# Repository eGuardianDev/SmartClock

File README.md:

# SmartClock
A small "smart" alarm clock for IoT course.

### Idea
A small clock with alarm and basic functions. Integrationg with WiFi via ESP32 for data sharing, maybe smart home automation. Different sensors for tracking enviroment data and sleep patterns.

### Restart of project
 - [ ] Change from arduino ide to platformio
 - [ ] Refactor RTC functions
 - [ ] Refactor display functions
 - [ ] Refactor pages system
 - [ ] Refactor bme280 sensors
 - [ ] Add sleep mode
 - [ ] Fix button design
 - [ ] Add lights for the display

## Documentation

### Tools
 - [Bit map to code](https://www.teachmemicro.com/lcd-bitmap-converter-online/)

### Parts
- Display: probably E-Ink or 7-segment.
- Sensors: Microphone for noise, temperature, humidity, light.
- Actuators control: attach lights and motor to make waking up easier.
- Main controller: ESP32

### Plans and ideas
- [X] Theoretical idea
- [X] Finding & ordering parts
  - [X] Finding compatable parts
  - [X] Making an order 
- [X] Testing parts and finding libraries
  - [X] Display 
    - E-Ink no touch 89x38cm - 296x128res [2.9" inch SPI](https://erelement.com/shop/e-ink-2-9-grey/)
  - [X] Sensors
    - ~~Microphone [Sound sensor wc](https://erelement.com/shop/sound-sensor-module/)~~
    - Enviroment [bme280](https://erelement.com/shop/bme280-ws/)
    - ~~Hand movement [qtr-md-08a](https://erelement.com/shop/qtr-md-08a/) [pir](https://erelement.com/shop/pir-sensor/)~~
    - light [photoresistor](https://elimex.bg/product/70488-fotorezistor-pgm5516-ldr5516)
    - ~~SD Card [reader](https://elimex.bg/product/75637-kit-k2162-micro-sd-kartochetets-za-uno)~~
  - [ ] ~~Actuators~~
  - [X] WiFi control 
- [X] Simple prototype
  - [X] WiFi server / API 
  - [X] Sensor and calibration
  - [ ] ~~Actuators connection~~
- [ ] Code
  - [X] Initialize everything
  - [X] Wifi connection
  - [X] Clock logic
  - [X] API logic 
    - [X] Weather 
    - [ ] Time sync 
    - [ ] Todo?
  - [ ] sleep tracking
  - [ ] calendar
  - [ ] Low-power/sleep mode 
- [X] Final design
  - [X] Container
  - [X] Compression of electronics
- [ ] Presentation material
  - [ ] Documentation 
    - [X] CAD design
    - [X] Schematics
    - [ ] Software
  - [X] Presentation
  - [X] Video?
  
### Current progress
 - [X] fix main page
 - [X] fix weather page
 - [ ] enter sleep mode
 - [X] add alarm
 - [X] test wifi provisioner
 - [ ] add time sync
 - [ ] hand move test
 - [ ] docs
 - [X] presentation

### problems met
 - bitmap size containment
 - system event configuration
 - hardware and electronics problem
 - usb charging
 - compilation time
 - interupts not fixed
 - maybe e-ink wasn't the best idea

### Settings and ideas
 - There should be different wake up patterns for the alarm. For example - ring 1 second, wait 3-5 seconds, repeat.
 - Extending the suspend button away, maybe using second ESP with ESP now protocol in deep sleep or unpowered.
 - sync alarm with phone
 - Weather forecast

### Diagram

### Main body CAD design

### Electronics schematics

### 3D PCB Design

### 3D render of all objects

---

Created for IoT Course FMI 2025.

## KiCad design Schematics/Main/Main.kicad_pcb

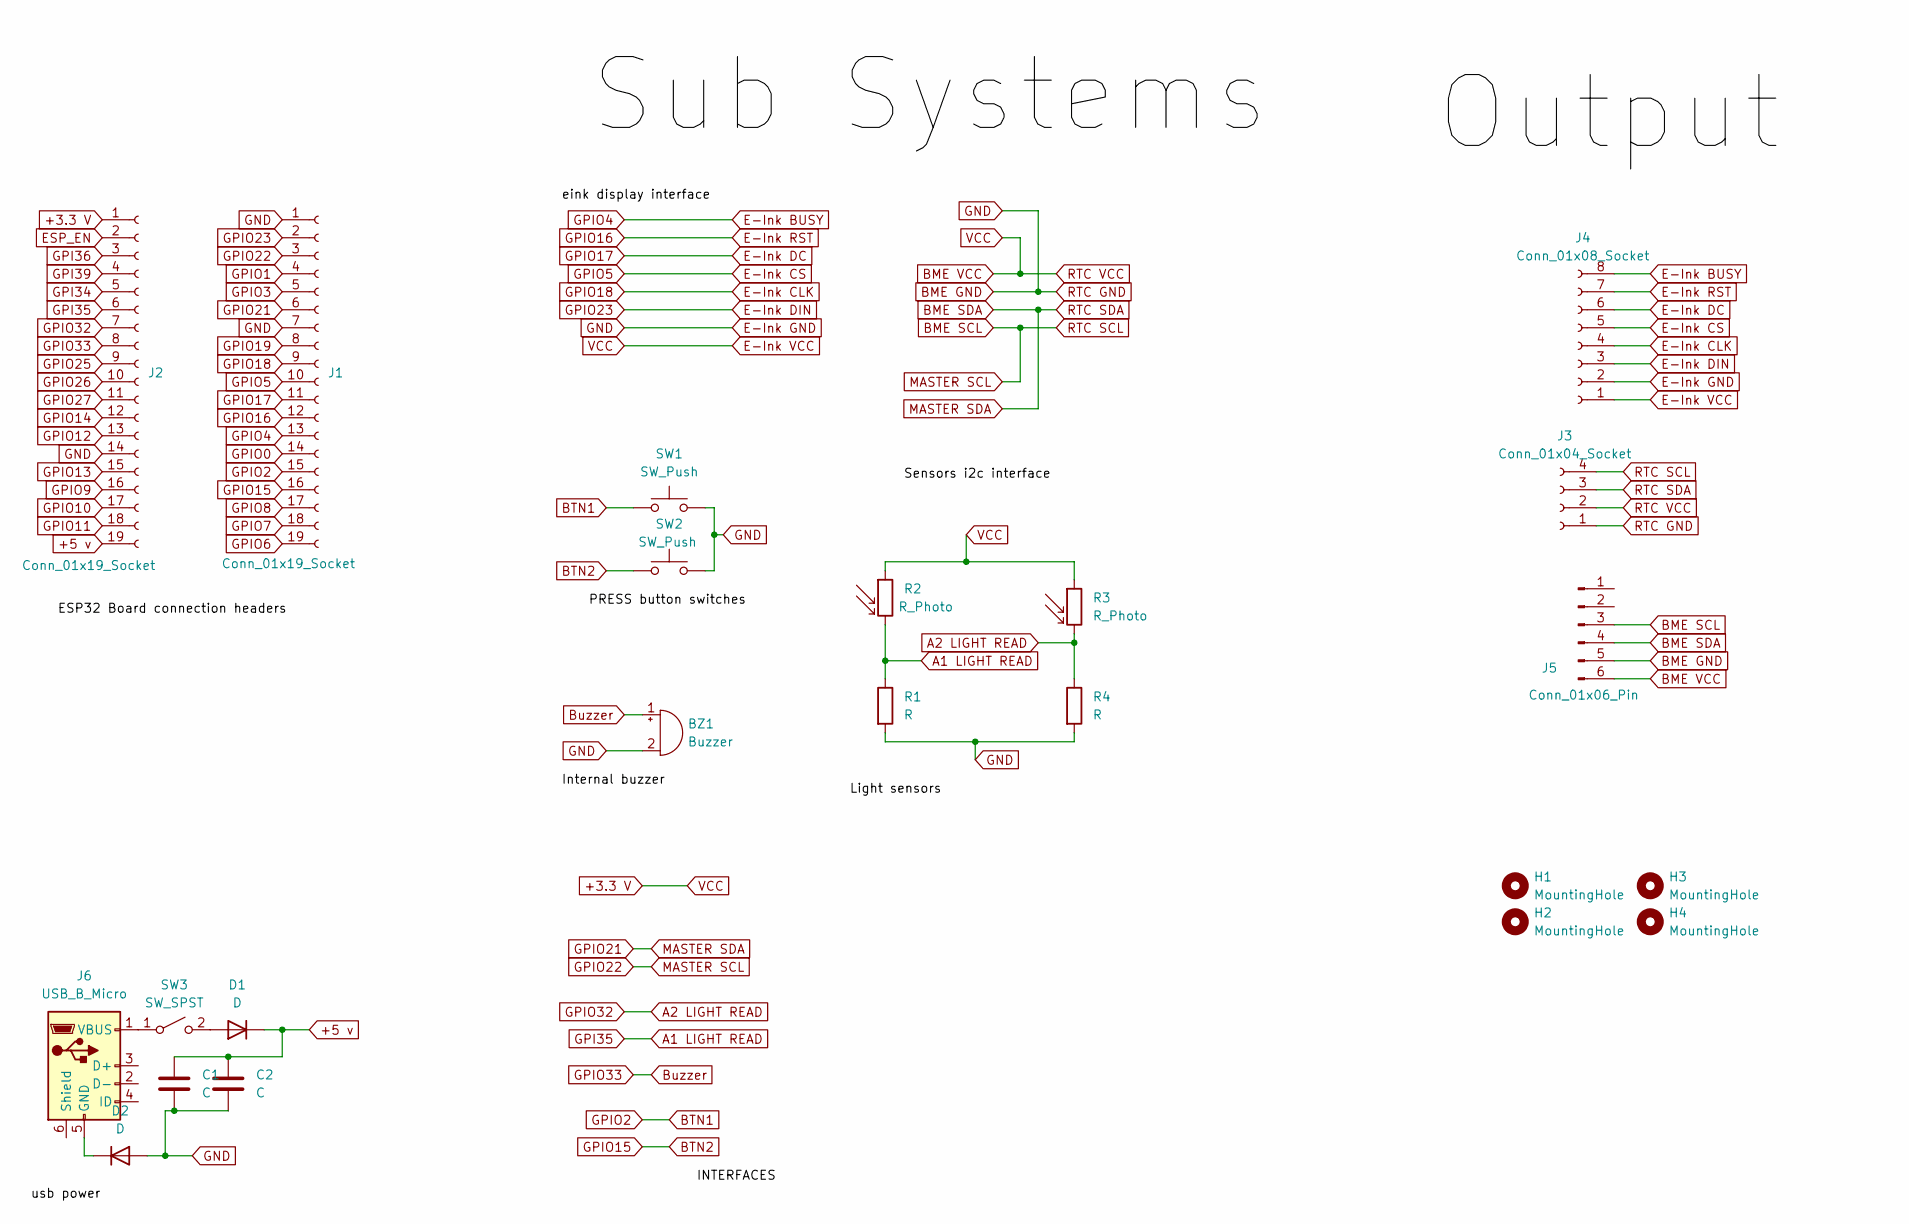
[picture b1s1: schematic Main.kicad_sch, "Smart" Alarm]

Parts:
BZ1: Buzzer; Buzzer_12x9.5RM7.6
C1: C; C_Radial_D5.0mm_H5.0mm_P2.00mm
C2: C; C_Disc_D3.0mm_W1.6mm_P2.50mm
D1, D2: D; D_DO-41_SOD81_P10.16mm_Horizontal
H1, H2, H3, H4: MountingHole; MountingHole_4mm
J1, J2: Conn_01x19_Socket; PinHeader_1x19_P2.54mm_Vertical
J3: Conn_01x04_Socket; PinHeader_1x04_P2.54mm_Vertical
J4: Conn_01x08_Socket; PinHeader_1x08_P2.54mm_Vertical
J5: Conn_01x06_Pin; PinHeader_1x06_P2.54mm_Vertical
J6: USB_B_Micro; USB_Micro-B_Amphenol_10103594-0001LF_Horizontal
R1, R4: R; R_Axial_DIN0207_L6.3mm_D2.5mm_P10.16mm_Horizontal
R2, R3: R_Photo; PinHeader_1x02_P2.54mm_Vertical
SW1, SW2: SW_Push; PinHeader_1x02_P2.54mm_Vertical
SW3: SW_SPST; PinHeader_1x02_P2.54mm_Vertical

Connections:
+3.3 V: J2.1, J3.2, J4.1, J5.6, R2.1, R3.1
+5 v: C1.1, C2.1, D1.1 (K), J2.19
A1 LIGHT READ: J2.6, R1.1, R2.2
A2 LIGHT READ: J2.7, R3.2, R4.1
BME GND: BZ1.2 (-), C1.2, C2.2, D2.2 (A), J1.1, J1.7, J2.14, J3.1, J4.2, J5.5, R1.2, R4.2, SW1.2, SW2.2
BME SCL: J1.3, J3.4, J5.3
BME SDA: J1.6, J3.3, J5.4
BTN1: J1.15, SW1.1
BTN2: J1.16, SW2.1
Buzzer: BZ1.1 (+), J2.8
E-Ink BUSY: J1.13, J4.8
E-Ink CLK: J1.9, J4.4
E-Ink CS: J1.10, J4.5
E-Ink DC: J1.11, J4.6
E-Ink DIN: J1.2, J4.3
E-Ink RST: J1.12, J4.7
ESP_EN: J2.2
GPI34: J2.5
GPI36: J2.3
GPI39: J2.4
GPIO0: J1.14
GPIO1: J1.4
GPIO3: J1.5
GPIO6: J1.19
GPIO7: J1.18
GPIO8: J1.17
GPIO9: J2.16
GPIO10: J2.17
GPIO11: J2.18
GPIO12: J2.13
GPIO13: J2.15
GPIO14: J2.12
GPIO19: J1.8
GPIO25: J2.9
GPIO26: J2.10
GPIO27: J2.11
unnamed: D1.2 (A), SW3.2 (B)
unnamed: D2.1 (K), J6.5 (GND)
unnamed: J6.1 (VBUS), SW3.1 (A)

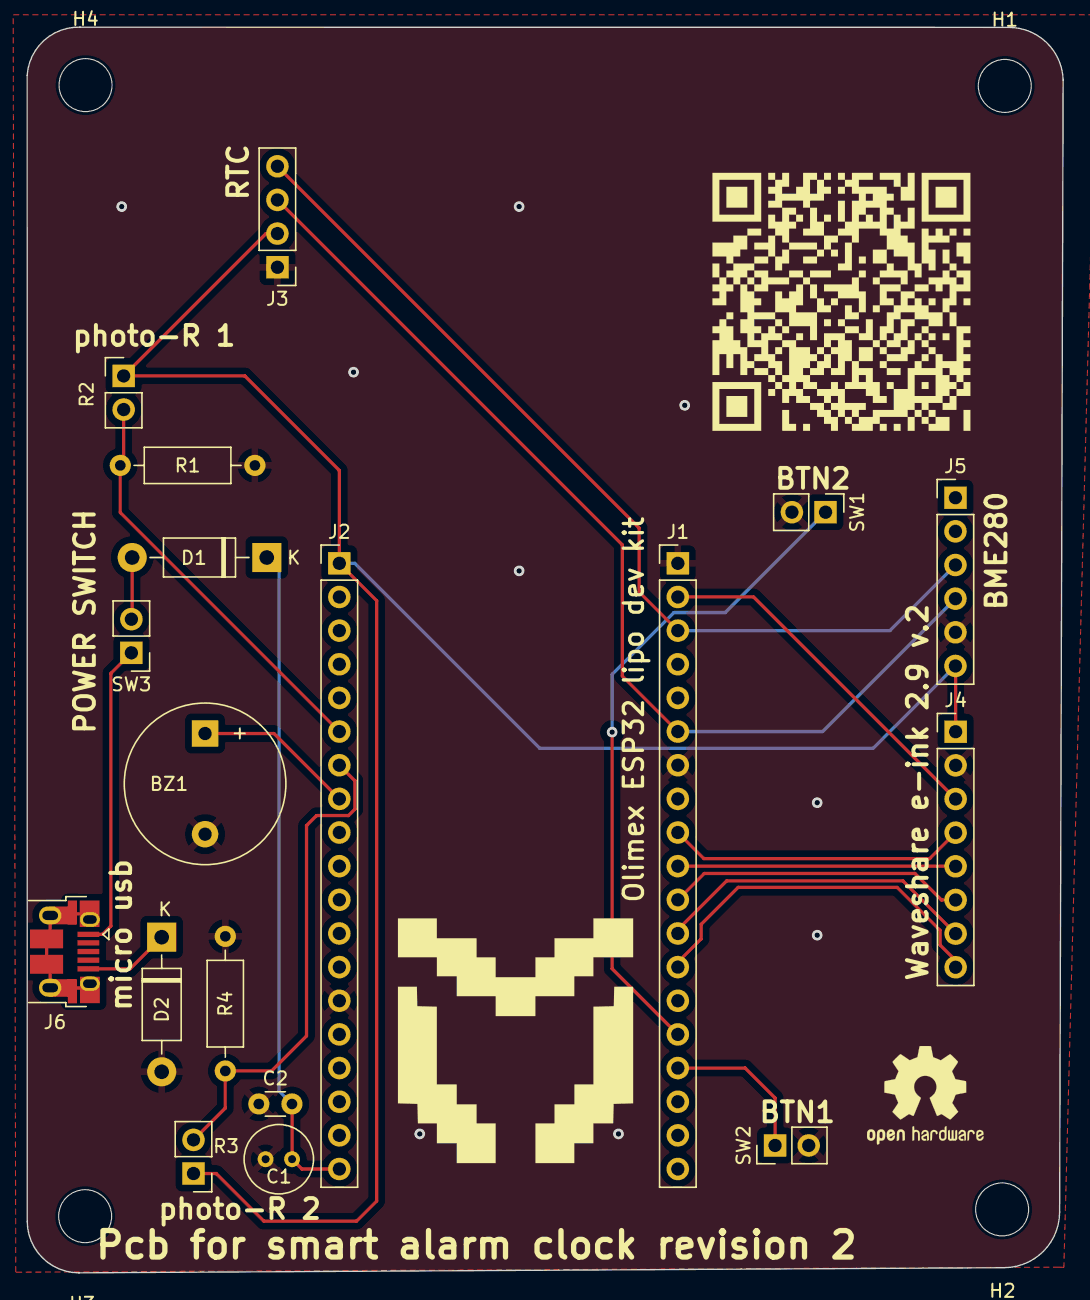
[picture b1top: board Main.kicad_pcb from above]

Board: 2 copper layers, 78.2 x 94.0 mm, 22 parts (0 on the bottom side), 19 nets.

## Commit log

2025-03-19 Initial Ideas
2025-03-24 some parts
2025-04-23 very basic code, diagram
2025-04-23 Fixed diagram img
2025-04-29 ordering parts, weather idea, sd card to buy
2025-05-02 CAD 3d design, schematics, docs
2025-05-02 organized, readme
2025-05-03 first print
2025-05-04 final cad system
2025-05-07 clock change time, temp display
2025-05-13 seperate pins in code, added buzzer, fixed pinout
2025-05-13 added missing format, change readme stuff
2025-05-21 basic wifi setup
2025-05-23 bitmap test
2025-05-23 Weather basic implementation, page changes, bitmaps
2025-05-23 bitmap, weather and page changes
2025-05-26 fixing gitignore
2025-05-26 stop tracking api
2025-05-26 test render
2025-05-26 gif test
2025-05-26 new font size, semi-ready clock page and weather page
2025-05-27 added web page for configuration
2025-05-28 presentation, and better website
2025-06-01 last updates for now
2025-07-05 PCB design and revision 2
2025-07-05 fixed format of pdf 3d render
2025-09-25 latest pcb
2025-12-04 plans
